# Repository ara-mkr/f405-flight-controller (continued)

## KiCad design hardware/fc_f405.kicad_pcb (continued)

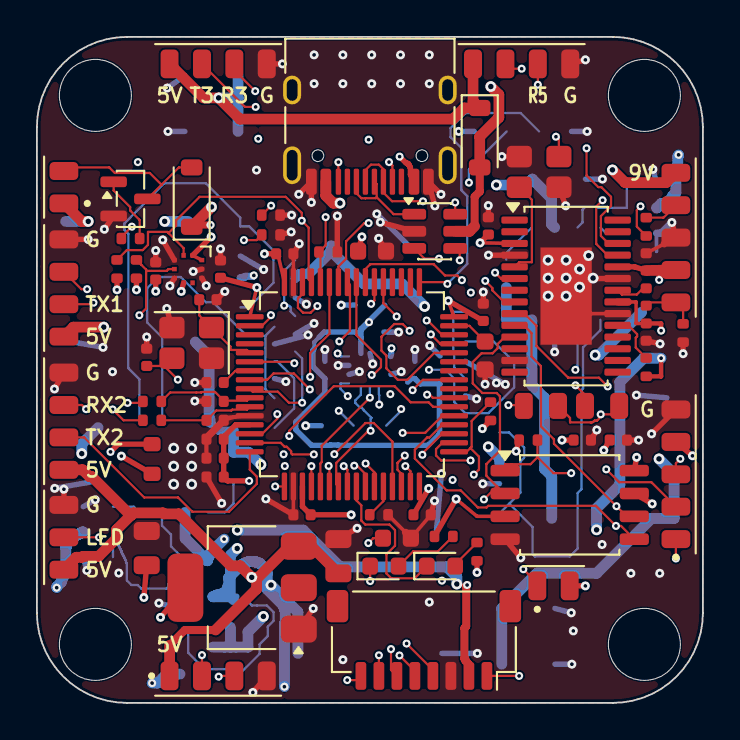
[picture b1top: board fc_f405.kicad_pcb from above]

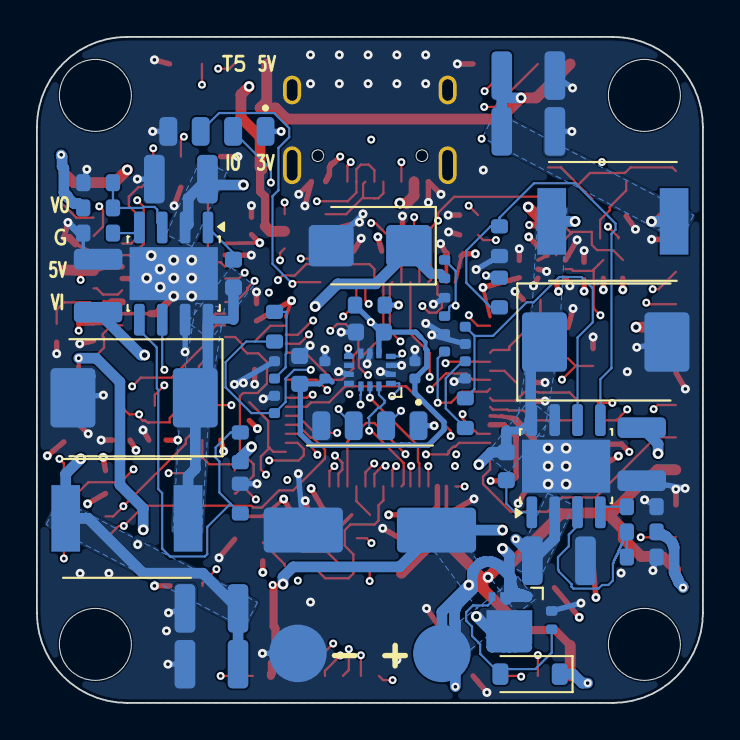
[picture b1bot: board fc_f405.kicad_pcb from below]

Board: 6 copper layers, 37.0 x 37.0 mm, 122 parts (49 on the bottom side), 90 nets.

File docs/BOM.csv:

refs,qty,value,mpn,lcsc,footprint,stock,type
"C1,C2,C3,C4",4,2.2uF/50V,1210B225K500NT,C1950,C_1210_3225Metric,11453,Extended
"C6,C7",2,47uF/10V,CS3225X7R476K100NRL,C5189825,C_1210_3225Metric,140829,Extended
"C8,C9",2,47uF/16V,CS3225X7R476K160NRL,C5440143,C_1210_3225Metric,93079,Extended
"C10,C11",2,0.1uF/25V,CC0603KRX7R9BB104,C14663,C_0603_1608Metric,12618106,Basic
C12,1,6800pF,0402B682K500NT,C1542,C_0402_1005Metric,118595,Preferred
C13,1,39pF,0402CG390J500NT,C1563,C_0402_1005Metric,149222,Extended
C14,1,33nF,0402B333K500NT,C507072,C_0402_1005Metric,170655,Extended
C15,1,47pF,0402CG470J500NT,C1567,C_0402_1005Metric,243432,Basic
C16,1,10uF/16V,GRM21BZ71C106KE15L,C162430,C_0805_2012Metric,114267,Extended
C17,1,22uF/10V,CL21A226MAQNNNE,C45783,C_0805_2012Metric,1734789,Basic
"C18,C19,C20,C21,C30,C31,C34,C35,C36,C37,C38,C40,C41,C42,C44,C45,C48",17,0.1uF,CL05B104KO5NNNC,C1525,C_0402_1005Metric,16407331,Basic
C23,1,4.7uF,GRM188Z71C475KE21D,C389010,C_0603_1608Metric,87761,Extended
"C24,C25,C32",3,2.2uF,GRM188R71A225KE15D,C86018,C_0603_1608Metric,459837,Extended
"C26,C49",2,1uF,GRM155R70J105KA12D,C88945,C_0402_1005Metric,451642,Extended
"C27,C33",2,10nF,CL05B103KB5NNNC,C15195,C_0402_1005Metric,2532413,Basic
"C28,C29",2,15pF,0402CG150J500NT,C1548,C_0402_1005Metric,358497,Basic
C39,1,10uF,CL10A106KP8NNNC,C19702,C_0603_1608Metric,5302559,Basic
C43,1,100uF/50V,UUD1H101MNL1GS,C116241,CP_Elec_8x10.5,174466,Extended
"C46,C47",2,22uF,CL21A226MAQNNNE,C45783,C_0805_2012Metric,1734789,Basic
"D1,D2",2,B560C-13-F,B560C-13-F,C85100,D_SMC,212196,Extended
D3,1,SMBJ30A,SMBJ30A,C19077584,D_SMB,301717,Preferred
D4,1,BZT52C15,BZT52C15,C2932746,D_SOD-123,273992,Extended
D5,1,1N4148W,1N4148W,C81598,D_SOD-123,3538406,Basic
D6,1,B5819W,B5819W SL,C8598,D_SOD-123,1059176,Basic
"FB1,FB2",2,600R/100MHz,GZ1608D601TF,C1002,R_0603_1608Metric,892564,Basic
J1,1,VBAT pads,Dia 3mm plated pads,,SolderPad_3mm_x2,,
J2,1,SWD pads,1.0mm pads,,SolderPad_1mm_x4,,
J3,1,BOOT pads,1.0mm pads,,SolderPad_1mm_x2,,
J4,1,I2C pads,ext compass,,SolderPad_1mm_x4,,
J5,1,USB-C 16P,TYPE-C 16PIN 2MD(073),C2765186,USB_C_Receptacle_HRO_TYPE-C-31-M-12,1171811,Extended
J6,1,JST-SH 8P,SM08B-SRSS-TB(LF)(SN),C160407,JST_SH_SM08B-SRSS-TB_1x08-1MP_P1.00mm_Horizontal,267231,Extended
J7,1,Buzzer pads,,,SolderPad_1mm_x2,,
J8,1,LED strip,,,SolderPad_1mm_x3,,
J9,1,Video pads,,,SolderPad_1mm_x6,,
J10,1,UART1 (RX),,,SolderPad_1mm_x4,,
J11,1,UART2 (GPS),,,SolderPad_1mm_x4,,
J12,1,UART3 (VTX),,,SolderPad_1mm_x4,,
J13,1,UART5,,,SolderPad_1mm_x4,,
J14,1,UART6,,,SolderPad_1mm_x4,,
J15,1,CAM/RSSI/U4TX,,,SolderPad_1mm_x5,,
L1,1,8.2uH,SMMS0630-8R2M,C128691,L_SMMS0630_7.1x6.6mm,12694,Extended
L2,1,22uH,SMMS0630-220M,C128694,L_SMMS0630_7.1x6.6mm,192695,Extended
LED1,1,GRN,XL-1608UGC-04,C965804,LED_0603_1608Metric,6367682,Extended
LED2,1,RED,XL-1608SURC-06,C965799,LED_0603_1608Metric,5989534,Extended
Q1,1,CJAE10P06,CJAE10P06,C2943210,PDFNWB-8L_3x3mm_DrainPad,18156,Extended
Q2,1,2N7002,2N7002K,C414015,SOT-23,3064287,Extended
"R1,R9",2,523k,FRC0603F5233TS,C5126197,R_0603_1608Metric,49470,Extended
"R2,R10",2,84.5k,FRC0603F8452TS,C2998081,R_0603_1608Metric,49863,Extended
"R3,R11",2,162k,FRC0603F1623TS,C2998114,R_0603_1608Metric,477208,Extended
R4,1,13.0k,0603WAF1302T5E,C22797,R_0603_1608Metric,388035,Basic
R5,1,53.6k,FRC0603F5362TS,C2930115,R_0603_1608Metric,90035,Extended
"R6,R7",2,10.2k,FRC0603F1022TS,C2933125,R_0603_1608Metric,776375,Extended
R8,1,105k,FRC0402F1053TS,C2933067,R_0603_1608Metric,282708,Extended
"R12,R22",2,100k,0402WGF1003TCE,C25741,R_0402_1005Metric,1535859,Basic
"R13,R16,R17,R18,R19,R23",6,10k,0402WGF1002TCE,C25744,R_0402_1005Metric,1256270,Basic
"R14,R15",2,4.7k,0402WGF4701TCE,C25900,R_0402_1005Metric,3285378,Basic
"R20,R21",2,5.1k,0402WGF5101TCE,C25905,R_0402_1005Metric,2237664,Basic
"R24,R25,R27,R28,R32",5,1k,0402WGF1001TCE,C11702,R_0402_1005Metric,2610919,Basic
"R29,R30",2,75R,0402WGF750JTCE,C25133,R_0402_1005Metric,306701,Preferred
R31,1,11.5k,0603WAF1152T5E,C25949,R_0603_1608Metric,173026,Extended
U1,1,STM32F405RGT7,STM32F405RGT7,C1337199,LQFP-64_10x10mm_P0.5mm,610,Extended
U2,1,ICM-42688-P,ICM-42688-P,C1850418,TDK_LGA-14_2.5x3.0mm,3920,Extended
U3,1,BMP388,BMP388,C779278,Bosch_LGA-10_2.0x2.0mm,15008,Extended
U4,1,AT7456E,AT7456E,C82351,HTSSOP-28-1EP_4.4x9.7mm_P0.65mm_EP2.85x5.4mm,33930,Extended
U5,1,W25Q128JVSIQ,W25Q128JVSIQ,C97521,SOIC-8_5.3x5.3mm_P1.27mm,94978,Basic
"U6,U7",2,TPS54360DDAR,TPS54360DDAR,C44377,SOIC-8-1EP_3.9x4.9mm_P1.27mm_EP2.95x4.9mm_Mask2.71x3.4mm,30171,Extended
U8,1,TLV1117-33IDCYR,TLV1117-33IDCYR,C37359,SOT-223-3_TabPin2,14146,Extended
U9,1,USBLC6-2SC6,USBLC6-2SC6,C2687116,SOT-23-6,150192,Extended
Y1,1,8MHz,TAXM8M4RDBCCT2T,C400090,Crystal_SMD_3225-4Pin_3.2x2.5mm,182379,Extended
Y2,1,27MHz,XL2EL89CMI-111YLC-27M,C19711726,Crystal_SMD_3225-4Pin_3.2x2.5mm,18258,Extended

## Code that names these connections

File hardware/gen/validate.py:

"""Cross-check every pin reference in design.py against the real symbol pin lists,
and against the STM32 LQFP64 pinout transcribed from ST DocID022152 Rev 4 Fig. 12."""
import sys, collections
sys.path.insert(0, '.')
import design, mksch

err = []
netpins = collections.defaultdict(list)
refs = collections.Counter()

for c in design.COMPONENTS:
    refs[c["ref"]] += 1
    have = set(mksch.sympins(c["lib"]))
    want = set(c["pins"])
    for p in want - have:
        err.append(f"{c['ref']} ({c['lib']}): pin '{p}' does not exist on the symbol")
    for p in have - want:
        pass  # unlisted pins become explicit no-connects; reported separately
    for p, n in c["pins"].items():
        if n and n != "!NC":
            netpins[n].append(f"{c['ref']}.{p}")

for r, n in refs.items():
    if n > 1: err.append(f"duplicate reference designator: {r} used {n} times")

# --- STM32F405RGT6/7 LQFP64, ST DocID022152 Rev 4, Figure 12 (p.39) ---
LQFP64 = {1:"VBAT",2:"PC13",3:"PC14",4:"PC15",5:"PH0",6:"PH1",7:"NRST",8:"PC0",9:"PC1",
 10:"PC2",11:"PC3",12:"VSSA",13:"VDDA",14:"PA0",15:"PA1",16:"PA2",17:"PA3",18:"VSS",
 19:"VDD",20:"PA4",21:"PA5",22:"PA6",23:"PA7",24:"PC4",25:"PC5",26:"PB0",27:"PB1",
 28:"PB2",29:"PB10",30:"PB11",31:"VCAP_1",32:"VDD",33:"PB12",34:"PB13",35:"PB14",
 36:"PB15",37:"PC6",38:"PC7",39:"PC8",40:"PC9",41:"PA8",42:"PA9",43:"PA10",44:"PA11",
 45:"PA12",46:"PA13",47:"VCAP_2",48:"VDD",49:"PA14",50:"PA15",51:"PC10",52:"PC11",
 53:"PC12",54:"PD2",55:"PB3",56:"PB4",57:"PB5",58:"PB6",59:"PB7",60:"BOOT0",61:"PB8",
 62:"PB9",63:"VSS",64:"VDD"}
# What DESIGN_PLAN sec 4 says each port pin must carry
PLAN = {"PA0":"UART4_TX","PA1":"UART4_RX","PA2":"UART2_TX","PA3":"UART2_RX",
 "PA4":"GYRO_CS","PA5":"SPI1_SCK","PA6":"SPI1_MISO","PA7":"SPI1_MOSI","PA8":"LED_STRIP",
 "PA11":"USB_DM","PA12":"USB_DP","PA13":"SWDIO","PA14":"SWCLK",
 "PB0":"MOTOR3","PB1":"MOTOR4","PB2":"BOOT1","PB3":"LED0","PB4":"MOTOR1","PB5":"MOTOR2",
 "PB6":"UART1_TX","PB7":"UART1_RX","PB8":"I2C1_SCL","PB9":"I2C1_SDA","PB10":"UART3_TX",
 "PB11":"UART3_RX","PB12":"OSD_CS","PB13":"SPI2_SCK","PB14":"SPI2_MISO","PB15":"SPI2_MOSI",
 "PC0":"FLASH_CS","PC1":"VBAT_SENSE","PC2":"CURR_SENSE","PC3":"RSSI_ADC","PC4":"GYRO_INT",
 "PC5":"LED1","PC6":"UART6_TX","PC7":"UART6_RX","PC8":"CAM_CTRL","PC12":"UART5_TX",
 "PD2":"UART5_RX","PC13":"BEEPER_GATE"}
mcu = next(c for c in design.COMPONENTS if c["ref"] == "U1")
for num, port in LQFP64.items():
    got = mcu["pins"].get(str(num))
    if port in PLAN:
        if got != PLAN[port]:
            err.append(f"U1 pin {num} ({port}): plan wants {PLAN[port]!r}, schematic has {got!r}")
    if got is None:
        err.append(f"U1 pin {num} ({port}) is missing from the pin map entirely")

print("=" * 70)
if err:
    print("VALIDATION FAILED - %d problem(s):" % len(err))
    for e in err: print("  *", e)
else:
    print("VALIDATION PASSED")
print("=" * 70)
print(f"{len(design.COMPONENTS)} components, {len(netpins)} nets")
single = sorted(n for n, p in netpins.items() if len(p) < 2)
if single:
    print(f"\nNets with fewer than 2 connections ({len(single)}):")
    for n in single: print(f"  {n}: {netpins[n]}")

# ---- geometric check: no two different nets may share a label/stub coordinate ----
import collections as _c
occupied = _c.defaultdict(set)
for c in design.COMPONENTS:
    pins = mksch.sympins(c["lib"])
    cx, cy = mksch.snap(c["at"])
    for pnum, pd in pins.items():
        net = c["pins"].get(pnum)
        if not net or net == "!NC": continue
        sx, sy = round(cx + pd["x"], 3), round(cy - pd["y"], 3)
        dx, dy = {0:(-1,0),180:(1,0),90:(0,1),270:(0,-1)}[int(pd["angle"]) % 360]
        for t in (0.0, 1.0):   # both the pin end and the label end
            px = round(sx + dx*mksch.STUB*t, 2); py = round(sy + dy*mksch.STUB*t, 2)
            occupied[(px, py)].add((net, f"{c['ref']}.{pnum}"))
clash = {k: v for k, v in occupied.items() if len({n for n, _ in v}) > 1}
print("\nGeometric collisions between different nets: %d" % len(clash))
for k, v in sorted(clash.items())[:15]:
    print(f"  at {k}: " + ", ".join(f"{n} ({r})" for n, r in sorted(v)))
offgrid = [(k, v) for k, v in occupied.items()
           if abs(k[0]/1.27 - round(k[0]/1.27)) > 1e-6 or abs(k[1]/1.27 - round(k[1]/1.27)) > 1e-6]
print("Off-grid endpoints: %d" % len(offgrid))
for k, v in offgrid[:5]: print("   ", k, list(v)[:1])

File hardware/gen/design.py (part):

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    "1":  "+3V3",                      # VBAT tied to 3V3, no RTC coin cell
    "31": "VCAP_1", "47": "VCAP_2",
    "7":  "NRST",  "60": "BOOT0",
    "5":  "OSC_IN", "6": "OSC_OUT",    # PH0 / PH1
    # -- UART4 (ESC telemetry) --
    "14": "UART4_TX", "15": "UART4_RX",          # PA0 PA1
    # -- USART2 (GPS) --
    "16": "UART2_TX", "17": "UART2_RX",          # PA2 PA3
    # -- SPI1, gyro only --
    "20": "GYRO_CS",  "21": "SPI1_SCK",          # PA4 PA5
    "22": "SPI1_MISO","23": "SPI1_MOSI",         # PA6 PA7
    "41": "LED_STRIP",                            # PA8  TIM1_CH1
    "42": "!NC", "43": "!NC",                     # PA9 PA10 spare
    "44": "USB_DM", "45": "USB_DP",               # PA11 PA12
    "46": "SWDIO", "49": "SWCLK",                 # PA13 PA14
    "50": "!NC",                                  # PA15 spare
    # -- port C --
    "8":  "FLASH_CS",                             # PC0
    "9":  "VBAT_SENSE", "10": "CURR_SENSE", "11": "RSSI_ADC",   # PC1 PC2 PC3
    "24": "GYRO_INT",  "25": "LED1",              # PC4 PC5
    "37": "UART6_TX", "38": "UART6_RX",           # PC6 PC7
    "39": "CAM_CTRL",                             # PC8  TIM8_CH3
    "40": "!NC",                                  # PC9  spare
    "51": "!NC", "52": "!NC",                     # PC10 PC11 spare
    "53": "UART5_TX",                             # PC12
    "2":  "BEEPER_GATE",                          # PC13
    "3":  "!NC", "4": "!NC",                      # PC14 PC15 OSC32, unused
    "54": "UART5_RX",                             # PD2
    # -- port B --
    "26": "MOTOR3", "27": "MOTOR4",               # PB0 PB1
    "28": "BOOT1",                                # PB2
    "55": "LED0",                                 # PB3  (JTDO, free once JTAG off)
    "56": "MOTOR1", "57": "MOTOR2",               # PB4 PB5
    "58": "UART1_TX", "59": "UART1_RX",           # PB6 PB7
    "61": "I2C1_SCL", "62": "I2C1_SDA",           # PB8 PB9
    "29": "UART3_TX", "30": "UART3_RX",           # PB10 PB11
    "33": "OSD_CS",                               # PB12
    "34": "SPI2_SCK", "35": "SPI2_MISO", "36": "SPI2_MOSI",     # PB13-15
    },
    "Package_QFP:LQFP-64_10x10mm_P0.5mm", "C1337199", "STM32F405RGT7",
    "https://www.st.com/resource/en/datasheet/stm32f405rg.pdf", rdy=52, vdy=-52)
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R("R28", "1k", (455, 490), "+3V3", "LED1_A", lcsc="C11702", mpn="0402WGF1001TCE")
add("LED2", "Device:LED", "RED", (470, 505), {"2": "LED1_A", "1": "LED1"},
    FP_LED, "C965799", "XL-1608SURC-06", rdy=6, vdy=-6)
# PC13 is limited to ~3 mA, so it drives a FET gate, never the buzzer itself
R("R23", "10k", (510, 450), "BEEPER_GATE", "Q2_G", lcsc="C25744", mpn="0402WGF1002TCE")
add("Q2", "Transistor_FET:Q_NMOS_GSD", "2N7002", (530, 470),
    {"1": "Q2_G", "2": "GND", "3": "BEEPER_DRAIN"}, FP_SOT23, "C414015", "2N7002K",
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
